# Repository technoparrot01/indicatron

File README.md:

# INDICATRON
Display/Clock with 100 4bit seven-segment 0.28 Inch indicators, RTC and Wi-Fi support.

Project is separated into two PCBs for modular design.\
Requires a 9–12V / 5A power supply.

[Bad apple on this](https://youtu.be/aoGiHarBVdQ)

# Animation example:

# Pictures:

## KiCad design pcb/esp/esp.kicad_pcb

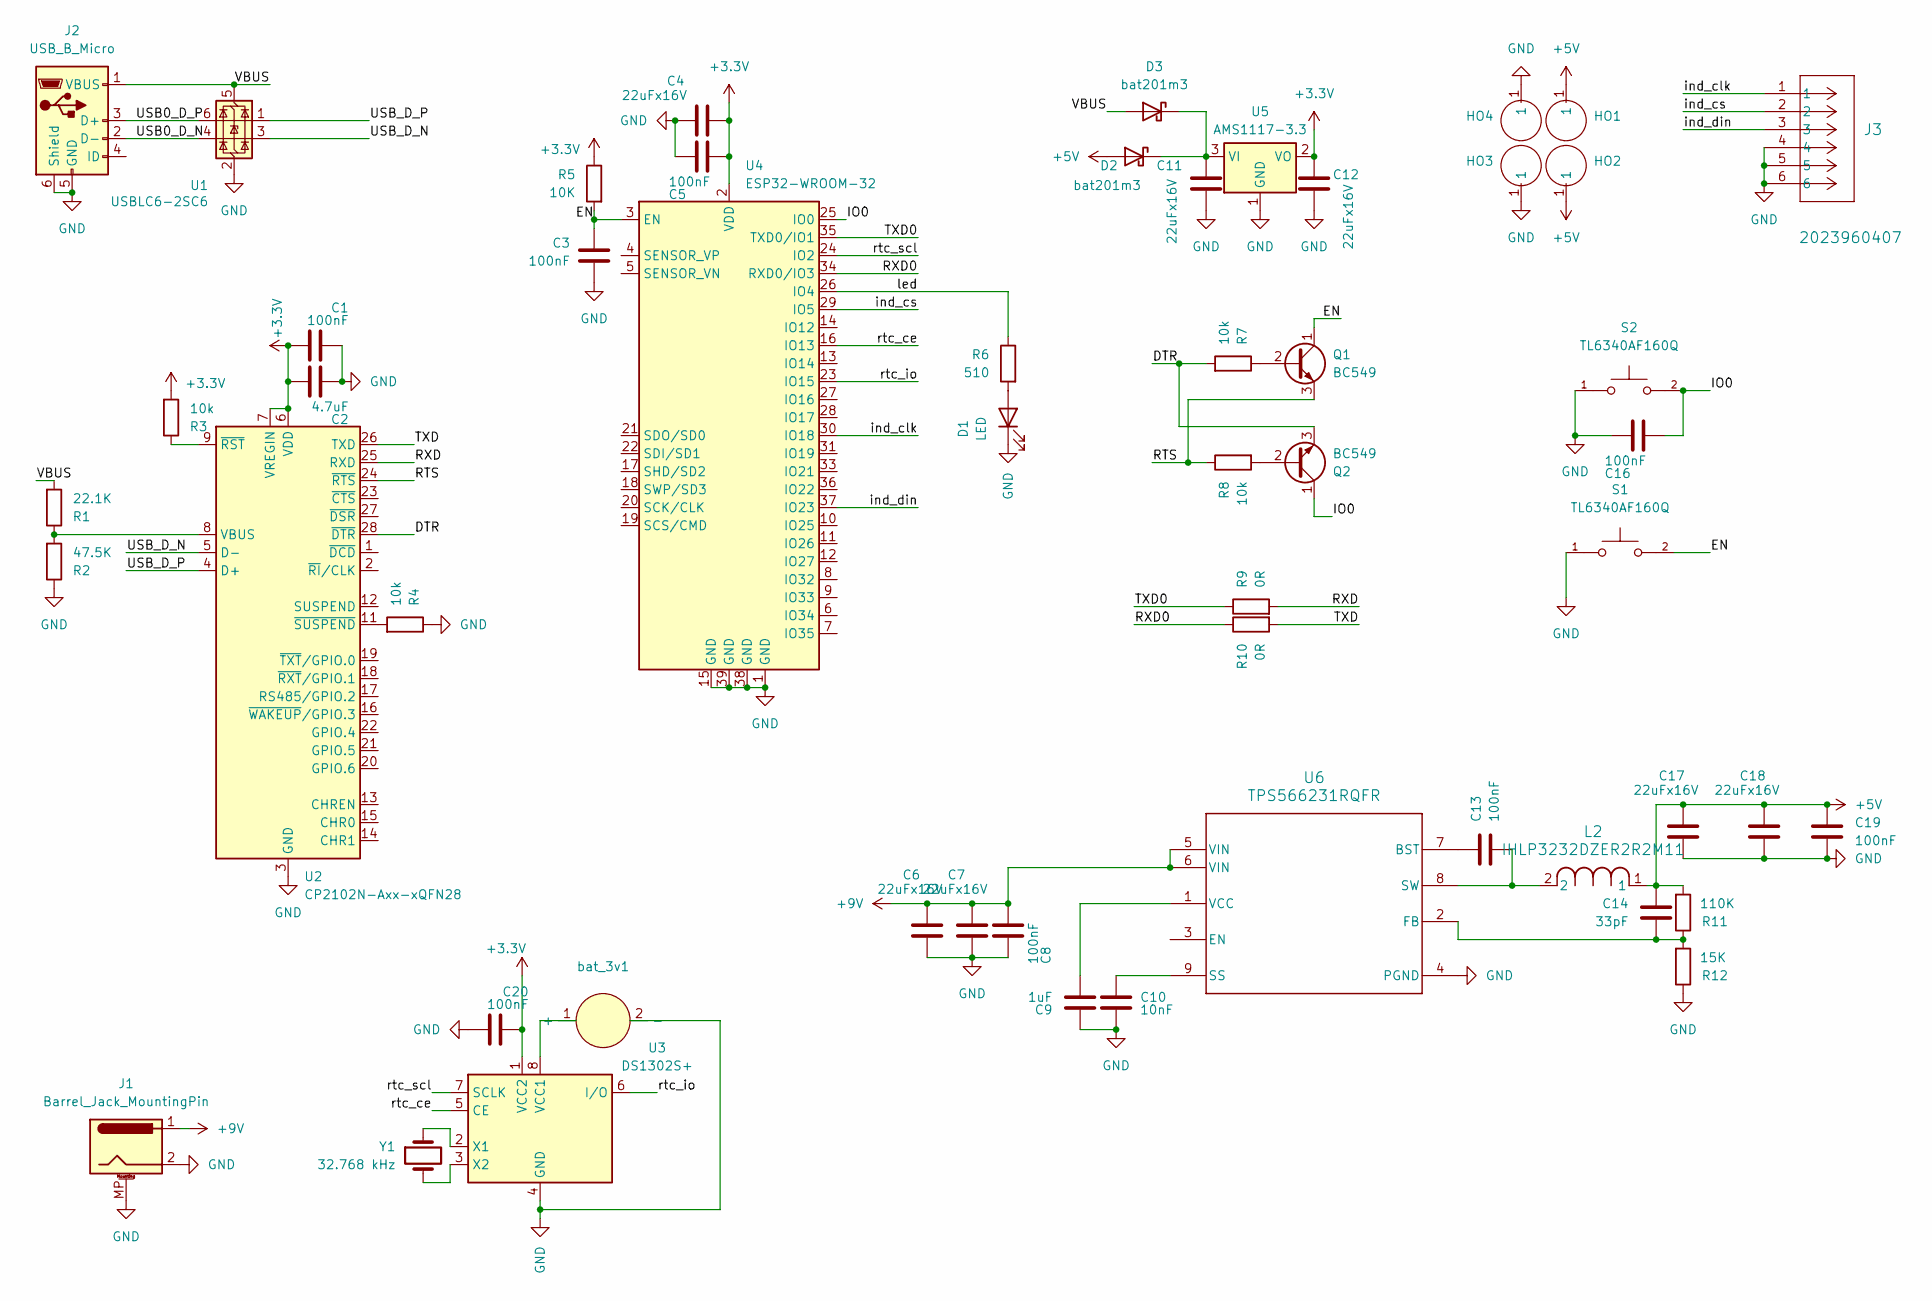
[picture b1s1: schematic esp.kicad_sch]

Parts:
C1, C3, C5, C8, C13, C16, C19, C20: 100nF; C_0603_1608Metric_Pad1.08x0.95mm_HandSolder
C2: 4.7uF; C_0603_1608Metric_Pad1.08x0.95mm_HandSolder
C4, C6, C7, C11, C12, C17, C18: 22uFx16V; C_1206_3216Metric_Pad1.33x1.80mm_HandSolder
C9: 1uF; C_0603_1608Metric_Pad1.08x0.95mm_HandSolder
C10: 10nF; C_0603_1608Metric_Pad1.08x0.95mm_HandSolder
C14: 33pF; C_0603_1608Metric_Pad1.08x0.95mm_HandSolder
D1: LED; LED_0603_1608Metric
D2, D3: bat201m3; D_SOD-323F
HO1, HO2, HO3, HO4: 9774030243R_HOLE
J1: Barrel_Jack_MountingPin; BarrelJack_CUI_PJ-063AH_Horizontal
J2: USB_B_Micro; USB_Micro-B_Amphenol_10118193-0002LF_Horizontal
J3: 2023960407; CON_2023960407
L2: IHLP3232DZER2R2M11; IND_IHLP-3232DZ_VIS
Q1, Q2: BC549; TO-92_Inline
R1: 22.1K; R_0603_1608Metric_Pad0.98x0.95mm_HandSolder
R2: 47.5K; R_0603_1608Metric_Pad0.98x0.95mm_HandSolder
R3, R4, R7, R8: 10k; R_0603_1608Metric_Pad0.98x0.95mm_HandSolder
R5: 10K; R_0603_1608Metric_Pad0.98x0.95mm_HandSolder
R6: 510; R_0603_1608Metric_Pad0.98x0.95mm_HandSolder
R9, R10: 0R; R_0603_1608Metric_Pad0.98x0.95mm_HandSolder
R11: 110K; R_0603_1608Metric_Pad0.98x0.95mm_HandSolder
R12: 15K; R_0603_1608Metric_Pad0.98x0.95mm_HandSolder
S1, S2: TL6340AF160Q; SW_TL6340AF160Q; PARTREV 10.23.2019
U1: USBLC6-2SC6; SOT-23-6
U2: CP2102N-Axx-xQFN28; QFN-28-1EP_5x5mm_P0.5mm_EP3.35x3.35mm
U3: DS1302S+; SO-8_5.3x6.2mm_P1.27mm
U4: ESP32-WROOM-32
U5: AMS1117-3.3; SOT-223-3_TabPin2
U6: TPS566231RQFR; RQF0009A
Y1: 32.768 kHz; Crystal_Round_D2.0mm_Vertical
bat_3v1: Battery_CR2032_3v_holder

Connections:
+3.3V: C1.1, C2.1, C4.1, C5.1, C12.1, C20.2, R3.2, R5.1, U2.6 (VDD), U2.7 (VREGIN), U3.1 (VCC2), U4.2 (VDD), U5.2 (VO)
+5V: C14.1, C17.1, C18.1, C19.1, D2.2 (A), HO1.1, HO2.1, L2.1, R11.2
+9V: C6.1, C7.1, C8.1, J1.1, U6.5 (VIN), U6.6 (VIN)
/DTR: Q2.3 (E), R7.2, U2.28 (~DTR)
/EN: C3.1, Q1.1 (C), R5.2, S1.2, U4.3 (EN)
/IO0: C16.1, Q2.1 (C), S2.2, U4.25 (IO0)
/RTS: Q1.3 (E), R8.1, U2.24 (~RTS)
/RXD: R9.2, U2.25 (RXD)
/RXD0: R10.1, U4.34 (RXD0/IO3)
/TXD: R10.2, U2.26 (TXD)
/TXD0: R9.1, U4.35 (TXD0/IO1)
/USB0_D_N: J2.2 (D-), U1.4 (I/O2)
/USB0_D_P: J2.3 (D+), U1.6 (I/O1)
/USB_D_N: U1.3 (I/O2), U2.5 (D-)
/USB_D_P: U1.1 (I/O1), U2.4 (D+)
/VBUS: D3.2 (A), J2.1 (VBUS), R1.2, U1.5 (VBUS)
/ind_clk: J3.1, U4.30 (IO18)
/ind_cs: J3.2, U4.29 (IO5)
/ind_din: J3.3, U4.37 (IO23)
/led: R6.1, U4.26 (IO4)
/rtc_ce: U3.5 (CE), U4.16 (IO13)
/rtc_io: U3.6 (I/O), U4.23 (IO15)
/rtc_scl: U3.7 (SCLK), U4.24 (IO2)
GND: C1.2, C2.2, C3.2, C4.2, C5.2, C6.2, C7.2, C8.2, C9.2, C10.2, C11.2, C12.2, C16.2, C17.2, C18.2, C19.2, C20.1, D1.1 (K), HO3.1, HO4.1, J1.2, J1.MP (MountPin), J2.5 (GND), J2.6 (Shield), J3.4, J3.5, J3.6, R2.1, R4.1, R12.1, S1.1, S2.1, U1.2 (GND), U2.3 (GND), U2.29 (GND), U3.4 (GND), U4.1 (GND), U4.15 (GND), U4.38 (GND), U4.39 (GND), U5.1 (GND), U6.4 (PGND), bat_3v1.2 (-)
unnamed: D1.2 (A), R6.2
unnamed: C11.1, D2.1 (K), D3.1 (K), U5.3 (VI)
unnamed: Q1.2 (B), R7.1
unnamed: Q2.2 (B), R8.2
unnamed: R1.1, R2.2, U2.8 (VBUS)
unnamed: R3.1, U2.9 (~RST)
unnamed: R4.2, U2.11 (~SUSPEND)
unnamed: U3.8 (VCC1), bat_3v1.1 (+)
unnamed: U3.2 (X1), Y1.1
unnamed: U3.3 (X2), Y1.2
unnamed: C13.1, U6.7 (BST)
unnamed: C14.2, R11.1, R12.2, U6.2 (FB)
unnamed: C10.1, U6.9 (SS)
unnamed: C13.2, L2.2, U6.8 (SW)
unnamed: C9.1, U6.1 (VCC)

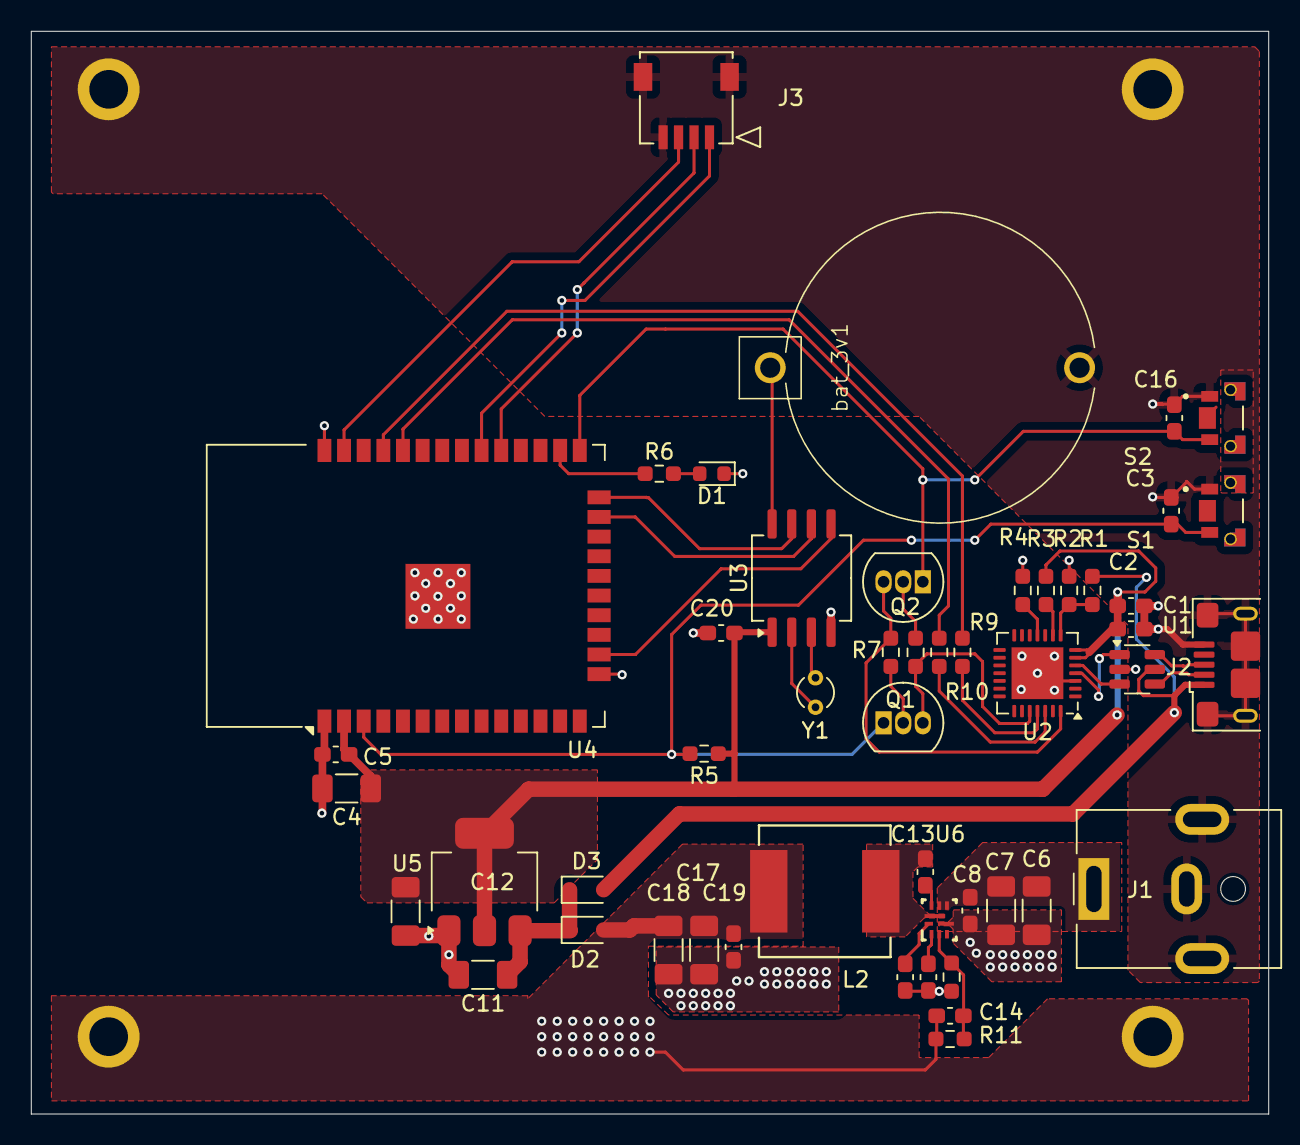
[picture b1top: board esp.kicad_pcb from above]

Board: 2 copper layers, 80.0 x 70.0 mm, 54 parts (0 on the bottom side), 39 nets.

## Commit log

2025-08-19 Add files via upload
    Firmware
2025-08-19 added gerber files
2025-08-19 added pcb's
2025-08-19 folder name change
2025-08-19 pictures added
2025-08-19 dvd2
2025-08-19 dvd3
2025-08-19 pictures
2025-08-19 added youtube link
2025-08-19 fixed link
2025-08-19 no shit more
